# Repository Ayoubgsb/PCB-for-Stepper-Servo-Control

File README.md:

# PCB-for-Stepper-Servo-Control
Hello everyone
this is PCB board for Stepper / Servo Control using stm32f411cue6 and 2 A4988 Stepper Motor Driver and servo motor driver 
to control 4 servo motors and 2 stepper motors 
i make connection between M1 M2 M3 of stepper motors with pin B0,1,10 so i can control the steps of the stepper motor from software side (full step 1/4 step , 1/8 , 1/16)
i used servo motor driver so in future we can add other servo motors without the need of changing the board and it only use i2c protocole to control the servo motor

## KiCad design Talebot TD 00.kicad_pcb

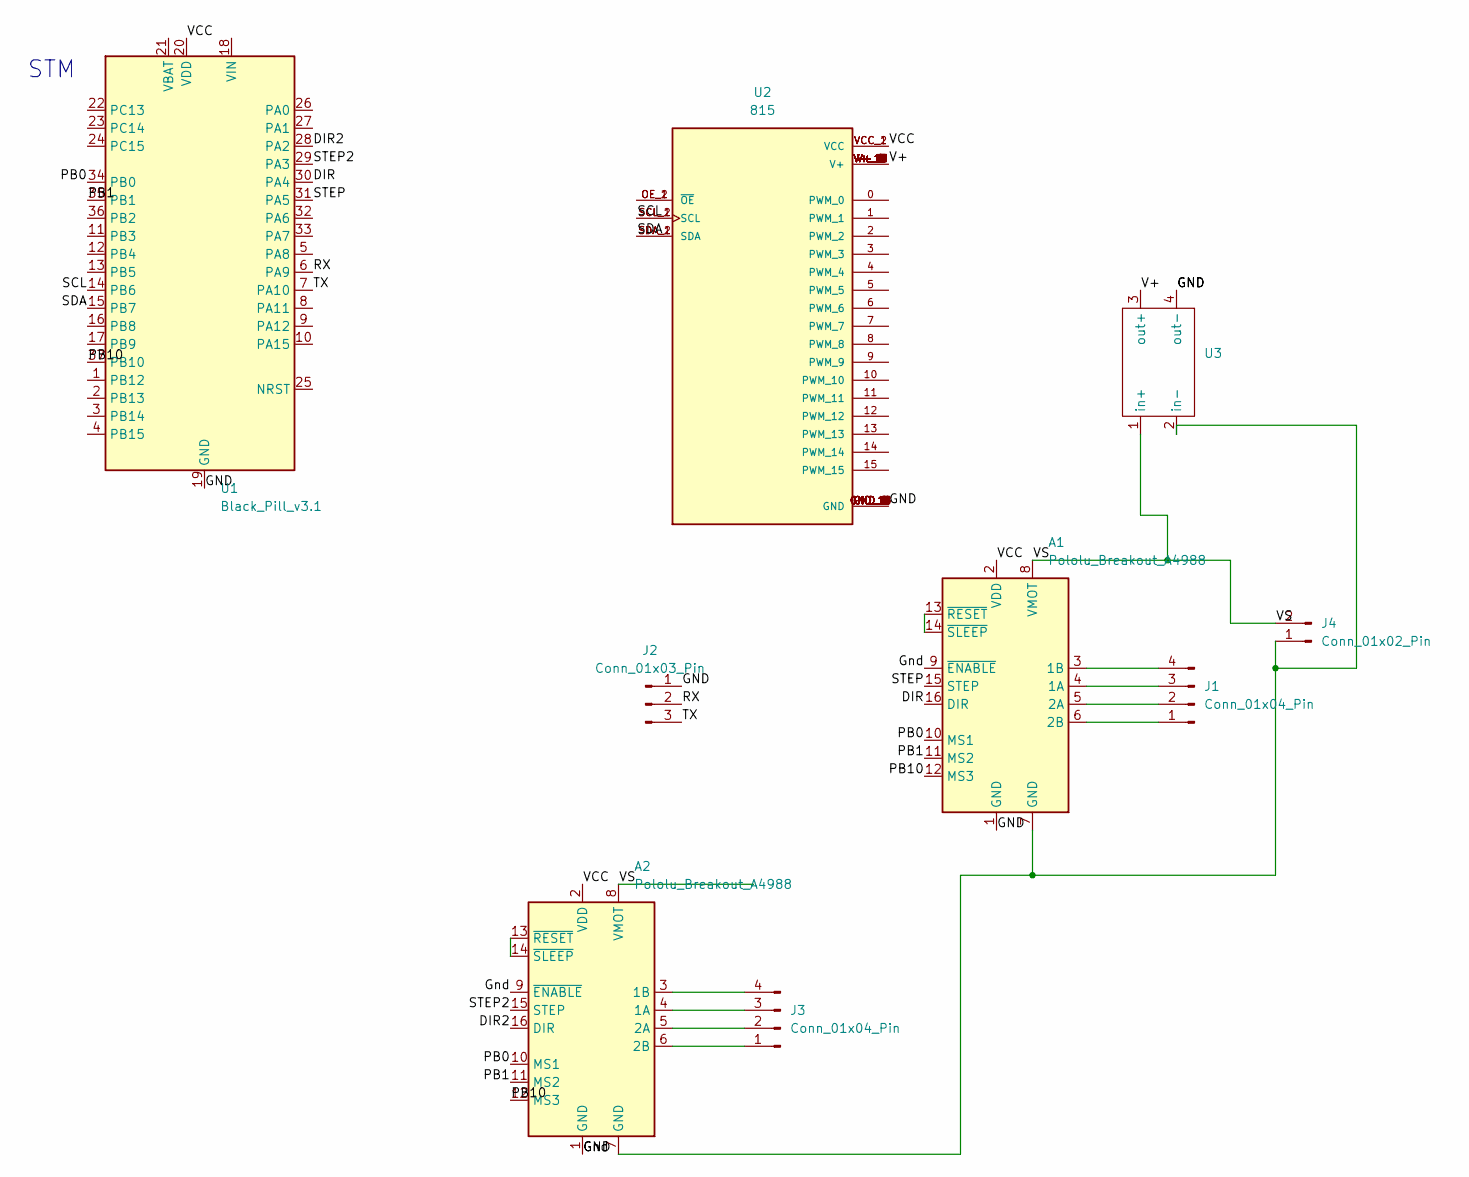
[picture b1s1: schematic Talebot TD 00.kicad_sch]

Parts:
A1, A2: Pololu_Breakout_A4988; Pololu_Breakout-16_15.2x20.3mm
J1, J3: Conn_01x04_Pin; PinHeader_1x04_P2.54mm_Vertical
J2: Conn_01x03_Pin; PinHeader_1x03_P2.00mm_Vertical
J4: Conn_01x02_Pin; AMASS_XT60-F_1x02_P7.20mm_Vertical
U1: Black_Pill_v3.1
U2: 815; MODULE_815; PARTREV C
U3: BUCK converture

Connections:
/DIR: A1.16 (DIR), U1.30 (PA4)
/DIR2: A2.16 (DIR), U1.28 (PA2)
/PB0: A1.10 (MS1), A2.10 (MS1), U1.34 (PB0)
/PB1: A1.11 (MS2), A2.11 (MS2), U1.35 (PB1)
/PB10: A1.12 (MS3), A2.12 (MS3), U1.37 (PB10)
/RX: J2.2, U1.6 (PA9)
/SCL: U1.14 (PB6), U2.SCL_1 (SCL), U2.SCL_2 (SCL)
/SDA: U1.15 (PB7), U2.SDA_1 (SDA), U2.SDA_2 (SDA)
/STEP: A1.15 (STEP), U1.31 (PA5)
/STEP2: A2.15 (STEP), U1.29 (PA3)
/TX: J2.3, U1.7 (PA10)
/V+: U2.V+_1 (V+), U2.V+_2 (V+), U2.V+_3 (V+), U2.V+_4 (V+), U2.V+_5 (V+), U2.V+_6 (V+), U2.V+_7 (V+), U2.V+_8 (V+), U2.V+_9 (V+), U2.V+_10 (V+), U2.V+_11 (V+), U2.V+_12 (V+), U2.V+_13 (V+), U2.V+_14 (V+), U2.V+_15 (V+), U2.V+_16 (V+), U2.V+_17 (V+), U2.V+_18 (V+), U3.3 (out+)
/VS: A1.8 (VMOT), A2.8 (VMOT), J4.2, U3.1 (in+)
GND: A1.1 (GND), A1.9 (~ENABLE), A2.1 (GND), A2.9 (~ENABLE), J2.1, U1.19 (GND), U1.39 (GND), U2.GND_1 (GND), U2.GND_2 (GND), U2.GND_3 (GND), U2.GND_4 (GND), U2.GND_5 (GND), U2.GND_6 (GND), U2.GND_7 (GND), U2.GND_8 (GND), U2.GND_9 (GND), U2.GND_10 (GND), U2.GND_11 (GND), U2.GND_12 (GND), U2.GND_13 (GND), U2.GND_14 (GND), U2.GND_15 (GND), U2.GND_16 (GND), U2.GND_17 (GND), U2.GND_18 (GND), U3.4 (out-)
unnamed: A1.4 (1A), J1.3
unnamed: A1.3 (1B), J1.4
unnamed: A1.5 (2A), J1.2
unnamed: A1.6 (2B), J1.1
unnamed: A1.13 (~RESET), A1.14 (~SLEEP)
unnamed: A2.4 (1A), J3.3
unnamed: A2.3 (1B), J3.4
unnamed: A2.5 (2A), J3.2
unnamed: A2.6 (2B), J3.1
unnamed: A2.13 (~RESET), A2.14 (~SLEEP)
unnamed: A1.7 (GND), A2.7 (GND), J4.1, U3.2 (in-)
unnamed: U2.OE_1 (~OE), U2.OE_2 (~OE)
VDD: A1.2 (VDD), A2.2 (VDD), U1.20 (VDD), U1.38 (VDD), U2.VCC_1 (VCC), U2.VCC_2 (VCC)
VIN: U1.18 (VIN), U1.40 (VIN)

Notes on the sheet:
STM

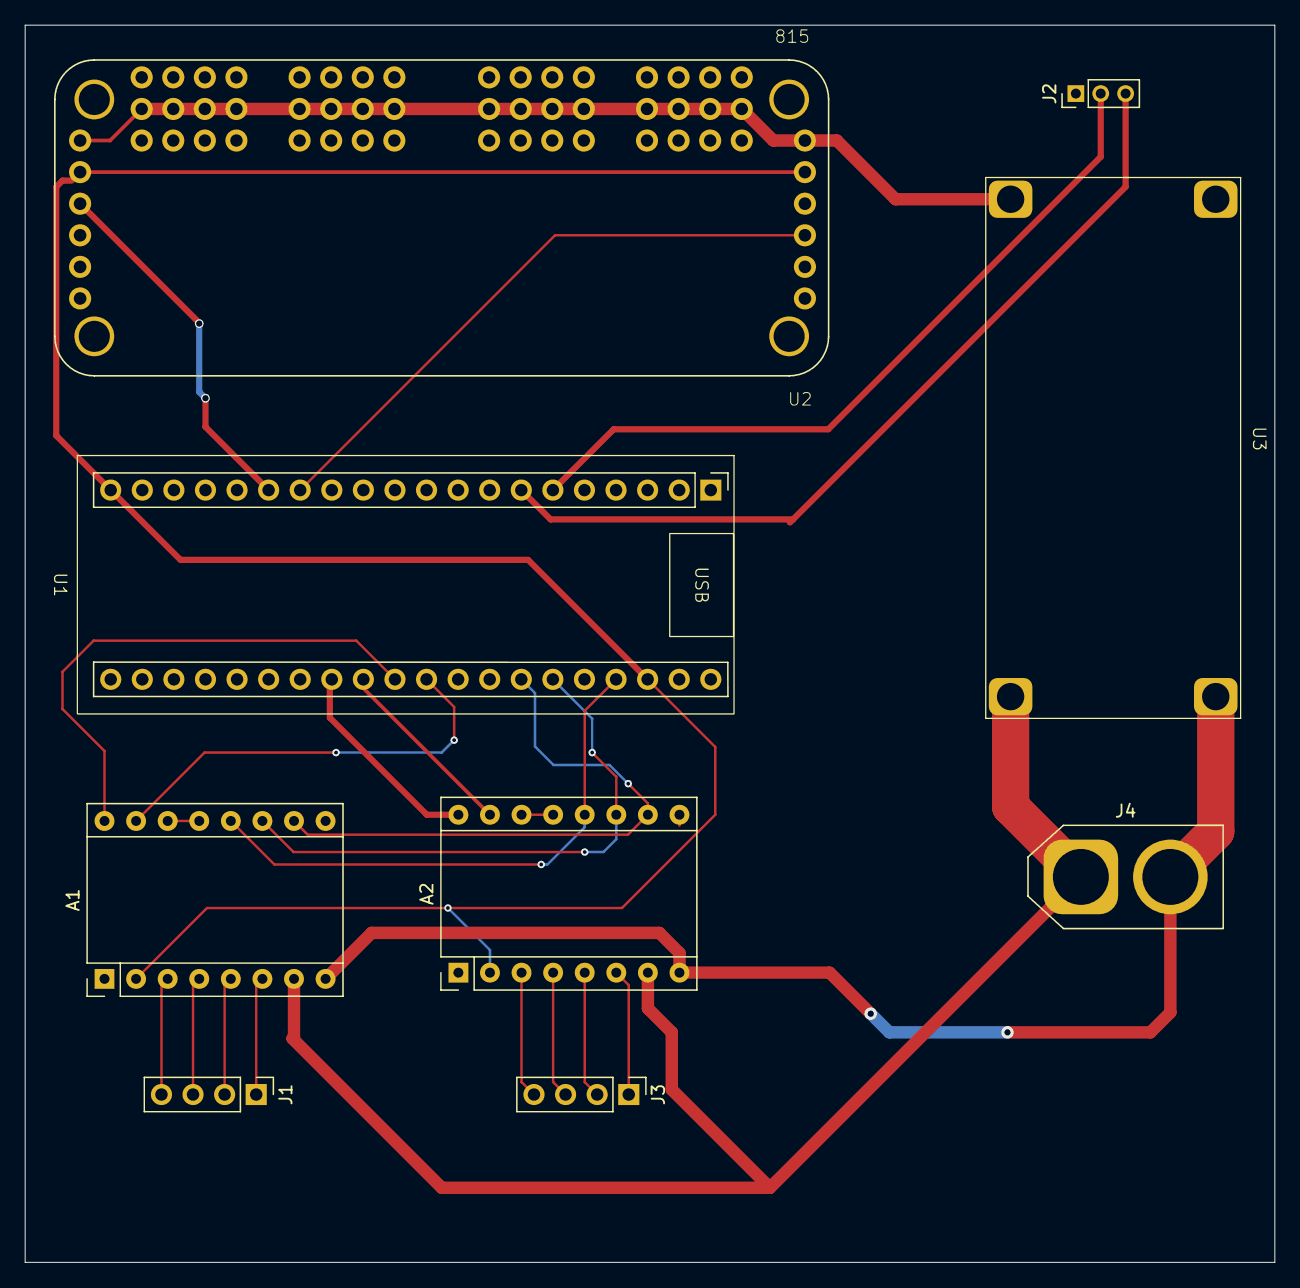
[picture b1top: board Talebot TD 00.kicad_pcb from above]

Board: 2 copper layers, 100.5 x 99.5 mm, 9 parts (0 on the bottom side), 28 nets.
